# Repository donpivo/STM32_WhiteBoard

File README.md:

Description: https://retronics.no/tag/stm32whiteboard/

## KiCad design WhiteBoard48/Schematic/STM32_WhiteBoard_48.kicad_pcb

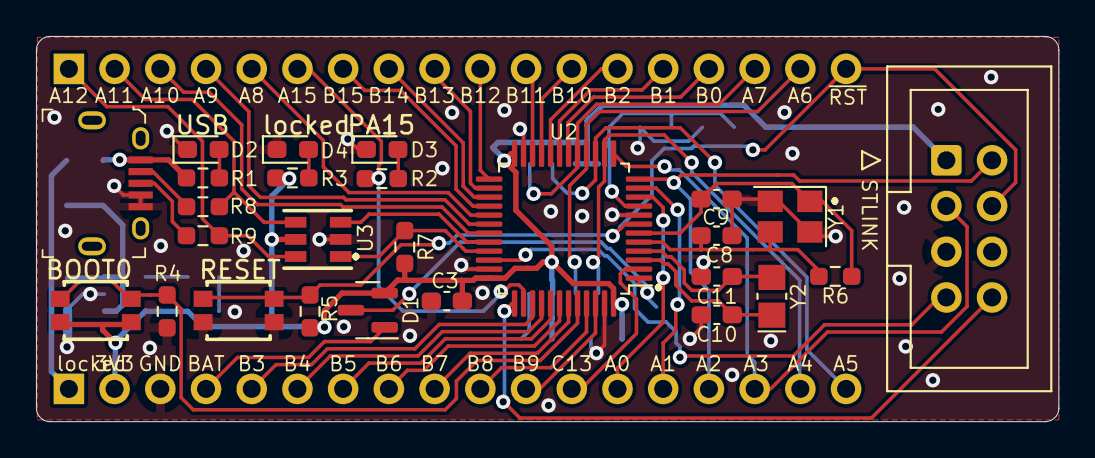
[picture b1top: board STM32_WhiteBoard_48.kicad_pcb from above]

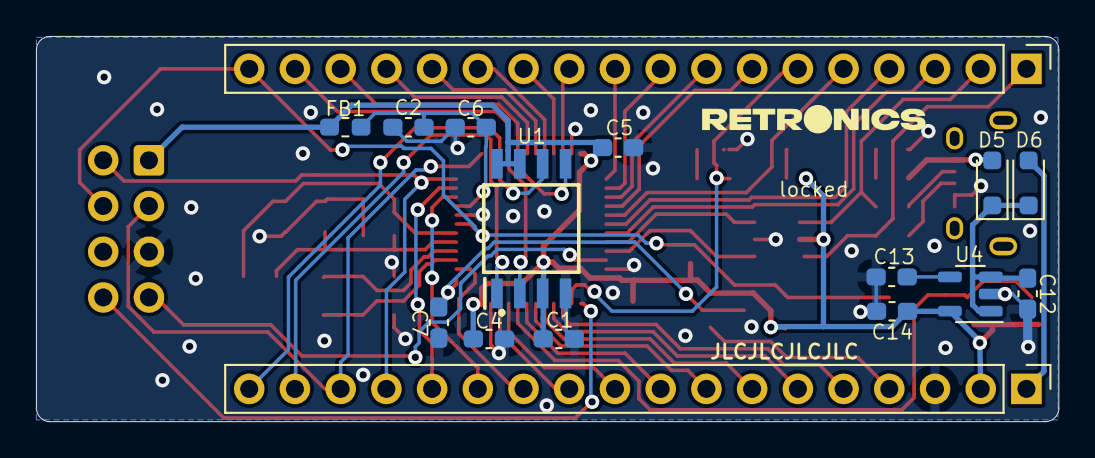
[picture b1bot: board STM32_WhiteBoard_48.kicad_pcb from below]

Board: 2 copper layers, 56.8 x 21.4 mm, 42 parts (16 on the bottom side), 55 nets.

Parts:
C1, C3, C4, C5, C6, C7: 100nF; C_0603_1608Metric_Pad1.08x0.95mm_HandSolder
C2, C12: 10µF; C_0603_1608Metric_Pad1.08x0.95mm_HandSolder
C8, C9, C10, C11: 20pF; C_0603_1608Metric_Pad1.08x0.95mm_HandSolder
C13: 10nF; C_0603_1608Metric_Pad1.08x0.95mm_HandSolder
C14: 1µF; C_0603_1608Metric_Pad1.08x0.95mm_HandSolder
D1: BAT54C; SOT-23
D2: "USB"; LED_0603_1608Metric_Pad1.05x0.95mm_HandSolder
D3: "PA15"; LED_0603_1608Metric_Pad1.05x0.95mm_HandSolder
D4: "3V3"; LED_0603_1608Metric_Pad1.05x0.95mm_HandSolder
D5, D6: B0520WS; D_SOD-323_HandSoldering
FB1: Ferrite_Bead_Small; L_0603_1608Metric_Pad1.05x0.95mm_HandSolder
J1: SWDIO+Serial; IDC-Header_2x04_P2.54mm_Vertical
J2: USB_B_Micro; USB_Micro_B_Female_10118194-0001LF
J3: Header2; PinHeader_1x18_P2.54mm_Vertical
J4: Header1; PinHeader_1x18_P2.54mm_Vertical
R1: 1kΩ; R_0603_1608Metric_Pad0.98x0.95mm_HandSolder
R2, R3: 330Ω; R_0603_1608Metric_Pad0.98x0.95mm_HandSolder
R4, R5: 10kΩ; R_0603_1608Metric_Pad0.98x0.95mm_HandSolder
R6: 1MΩ; R_0603_1608Metric_Pad0.98x0.95mm_HandSolder
R7: 1.5kΩ; R_0603_1608Metric_Pad0.98x0.95mm_HandSolder
R8, R9: 20Ω; R_0603_1608Metric_Pad0.98x0.95mm_HandSolder
SW1: BOOT0; SKTHACE010
SW2: RESET; SKTHACE010
U1: W25Q32JVSSIQ
U2: STM32F103CBTx; LQFP-48_7x7mm_P0.5mm
U3: USBLC6-2P6; USBLC6-2SC6
U4: LD3985M33R_SOT23; SOT-23-5
Y1: XC32M4-8.000; Crystal_SMD_3225-4Pin_3.2x2.5mm
Y2: CM8V-T1A-32.768KHZ-12.5PF; Crystal_SMD_MicroCrystal_CC8V-T1A-2Pin_2.0x1.2mm_HandSolder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

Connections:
+3.3V: C1.2, C3.1, C4.1, C5.1, C14.2, D1.2, FB1.2, J1.1, J4.2, R3.2, R5.2, R7.1, SW1.2, U1.3 (~WP), U1.7 (~RST), U1.8 (VCC), U2.24 (3V3), U2.36 (3V3), U2.48 (3V3), U3.5 (VBUS), U4.5 (VOUT)
+5V: D6.2 (A), J4.1
GND: C1.1, C2.1, C3.2, C4.2, C5.2, C6.1, C7.1, C8.1, C9.1, C10.2, C11.1, C12.1, C13.1, C14.1, D2.1 (K), D3.1 (K), D4.1 (K), J1.5, J2.4 (ID), J2.5 (GND), J4.3, R4.1, SW2.2, U1.4 (GND), U2.8 (GNDA), U2.23 (GND), U2.35 (GND), U2.47 (GND), U3.2 (GND), U4.2 (GND), Y1.2, Y1.4
unnamed: D2.2 (A), R1.1
unnamed: D3.2 (A), R2.1
unnamed: D4.2 (A), R3.1
unnamed: C12.2, D5.1 (K), D6.1 (K), U4.1 (VIN), U4.3 (INH)
unnamed: J2.3 (D+), R9.2
unnamed: J2.2 (D-), R8.2
unnamed: C2.2, C6.2, FB1.1, U2.9 (3V3A)
unnamed: R4.2, SW1.1, U2.44 (BOOT0)
unnamed: C10.1, U2.3 (OSC32K_A), Y2.1
unnamed: C11.2, U2.4 (OSC32K_B), Y2.2
unnamed: C8.2, R6.2, U2.5 (OSC_8M_A), Y1.3
unnamed: C9.2, R6.1, U2.6 (OSC_8M_B), Y1.1
unnamed: U2.32 (PA11_USB-), U3.3 (I/O2)
unnamed: R7.2, U2.33 (PA12_USB+), U3.1 (I/O1)
unnamed: C7.2, D1.3, U2.1 (VBAT)
unnamed: C13.2, U4.4 (BYP)
PA0: J4.13, U2.10 (PA0_ADC0_PWM)
PA1: J4.14, U2.11 (PA1_ADC1_PWM)
PA2_TX2: J1.2, J4.15, U2.12 (PA2_ADC2_TX2_PWM)
PA3_RX2: J1.3, J4.16, U2.13 (PA3_ADC3_RX2_PWM)
PA4_CS: J4.17, U1.1 (~CS), U2.14 (PA4_ADC4_SS1)
PA5_SCK1: J4.18, U1.6 (CLK), U2.15 (PA5_ADC5_SCK1)
PA6_MISO1: J3.17, U1.2 (DO), U2.16 (PA6_ADC6_MISO1_PWM)
PA7_MOSI1: J3.16, U1.5 (DI), U2.17 (PA7_ADC7_MOSI1_PWM)
PA8: J3.5, U2.29 (PA8_PWM)
PA9: J3.4, U2.30 (PA9_TX1_PWM)
PA10: J3.3, U2.31 (PA10_RX1_PWM)
PA11_USB-: J3.2, R8.1, U3.4 (I/O2)
PA12_USB+: J3.1, R9.1, U3.6 (I/O1)
PA13_SWDIO: J1.7, U2.34 (PA13_SWDIO)
PA14_SWCLK: J1.8, U2.37 (PA14_SWCLK)
PA15_LED: J3.6, R2.2, U2.38 (PA15)
PB0: J3.15, U2.18 (PB0_ADC8_PWM)
PB1: J3.14, U2.19 (PB1_ADC9_PWM)
PB2: J3.13, U2.20 (PB2)
PB3: J4.5, U2.39 (PB3_SCK1)
PB4: J4.6, U2.40 (PB4_MISO1)
PB5: J4.7, U2.41 (PB5_MOSI1)
PB6: J4.8, U2.42 (PB6_TX1_SCL1_PWM)
PB7: J4.9, U2.43 (PB7_RX1_SDA1_PWM)
PB8: J4.10, U2.45 (PB8_SCL1_PWM)
PB9: J4.11, U2.46 (PB9_SDA1_PWM)
PB10: J3.12, U2.21 (PB10_SCL2_TX3)
PB11: J3.11, U2.22 (PB11_SDA2_RX3)
PB12: J3.10, U2.25 (PB12_SS2)
PB13: J3.9, U2.26 (PB13_SCK2)
PB14: J3.8, U2.27 (PB14_MISO2)
PB15: J3.7, U2.28 (PB15_MOSI2)
PC13: J4.12, U2.2 (PC13)
RTC_BATT: D1.1, J4.4
VBUS: D5.2 (A), J2.1 (VBUS), R1.2
~RESET: J1.4, J3.18, R5.1, SW2.1, U2.7 (~RST)

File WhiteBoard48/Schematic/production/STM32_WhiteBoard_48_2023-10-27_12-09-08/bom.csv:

Designator,Footprint,Quantity,Value,LCSC Part #
"C1, C3, C4, C5, C6, C7",0603,6,100nF,
"C10, C11, C8, C9",0603,4,20pF,
"C12, C2",0603,2,10µF,
C13,0603,1,10nF,
C14,0603,1,1µF,
D1,SOT-23,1,BAT54C,
D2,0603,1,"""USB""",
D3,0603,1,"""PA15""",
D4,0603,1,"""3V3""",
"D5, D6",D_SOD-323_HandSoldering,2,B0520WS,
FB1,0603,1,Ferrite_Bead_Small,
J1,IDC-Header_2x04_P2.54mm_Vertical,1,SWDIO+Serial,
J2,USB_Micro_B_Female_10118194-0001LF,1,USB_B_Micro,
J3,PinHeader_1x18_P2.54mm_Vertical,1,Header2,
J4,PinHeader_1x18_P2.54mm_Vertical,1,Header1,
R1,0603,1,1kΩ,
"R2, R3",0603,2,330Ω,
"R4, R5",0603,2,10kΩ,
R6,0603,1,1MΩ,
R7,0603,1,1.5kΩ,
"R8, R9",0603,2,20Ω,
SW1,SKTHACE010,1,BOOT0,
SW2,SKTHACE010,1,RESET,
U1,W25Q32JVSSIQ,1,W25Q32JVSSIQ,
U2,LQFP-48_7x7mm_P0.5mm,1,STM32F103CBTx,
U3,USBLC6-2SC6,1,USBLC6-2P6,
U4,SOT-23-5,1,LD3985M33R_SOT23,
Y1,Crystal_SMD_3225-4Pin_3.2x2.5mm,1,XC32M4-8.000,
Y2,Crystal_SMD_MicroCrystal_CC8V-T1A-2Pin_2.0x1.2mm_HandSoldering,1,CM8V-T1A-32.768KHZ-12.5PF,

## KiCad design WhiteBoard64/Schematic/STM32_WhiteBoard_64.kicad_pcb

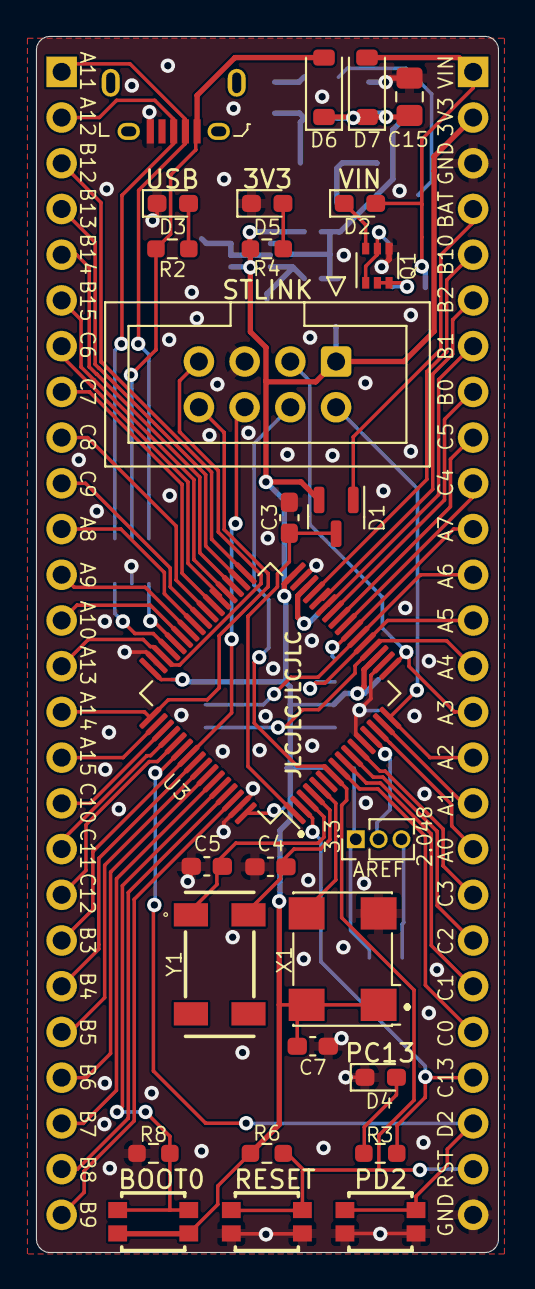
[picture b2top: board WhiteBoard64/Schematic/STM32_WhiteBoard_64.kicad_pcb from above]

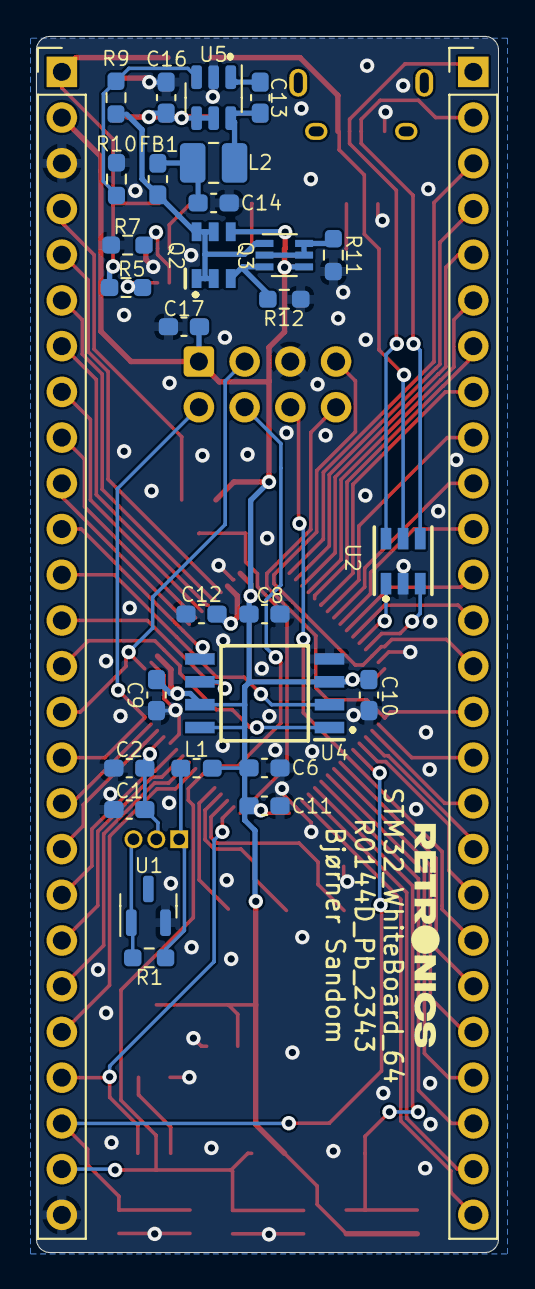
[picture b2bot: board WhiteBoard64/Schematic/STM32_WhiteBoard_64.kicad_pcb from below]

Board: 2 copper layers, 25.7 x 67.6 mm, 57 parts (30 on the bottom side), 77 nets.

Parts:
C1, C12: 4.7µF; C_0603_1608Metric_Pad1.08x0.95mm_HandSolder
C2, C3, C6, C7, C8, C9, C10, C11, C13, C16: 100nF; C_0603_1608Metric_Pad1.08x0.95mm_HandSolder
C4, C5: 4.7pF; C_0603_1608Metric_Pad1.08x0.95mm_HandSolder
C14, C17: 10µF 16V; C_0603_1608Metric_Pad1.08x0.95mm_HandSolder
C15: 10µF 50V; C_0805_2012Metric_Pad1.18x1.45mm_HandSolder
D1: BAT54C; SOT-23
D2: "VIN"; LED_0603_1608Metric_Pad1.05x0.95mm_HandSolder
D3: "USB"; LED_0603_1608Metric_Pad1.05x0.95mm_HandSolder
D4: "PC13"; LED_0603_1608Metric_Pad1.05x0.95mm_HandSolder
D5: "3V3"; LED_0603_1608Metric_Pad1.05x0.95mm_HandSolder
D6, D7: 1N5819W; D_SOD-123
FB1: 100Ω@100MHz; L_0603_1608Metric_Pad1.05x0.95mm_HandSolder
J1: SWDIO+Serial; IDC-Header_2x04_P2.54mm_Vertical
J2: USB_B_Micro; USB_Micro_B_Female_10118194-0001LF
J3: Header2; PinHeader_1x26_P2.54mm_Vertical
J4: Header1; PinHeader_1x26_P2.54mm_Vertical
JP1: Jumper_3_Bridged12; PinHeader_1x03_P1.27mm_Vertical
L1: 22µH 2.4Ω; L_0603_1608Metric_Pad1.05x0.95mm_HandSolder
L2: 6.8µH 1A; L_1008_2520Metric_Pad1.43x2.20mm_HandSolder
Q1: BC847BS; SOT-363_SC-70-6
Q2: Si3493DDV; SOT95P280X100-6N
Q3: BC857BS; SOT-363_SC-70-6-Handsoldering
R1: 220Ω; R_0603_1608Metric_Pad0.98x0.95mm_HandSolder
R2: 1kΩ; R_0603_1608Metric_Pad0.98x0.95mm_HandSolder
R3, R4: 330Ω; R_0603_1608Metric_Pad0.98x0.95mm_HandSolder
R5: 47kΩ; R_0603_1608Metric_Pad0.98x0.95mm_HandSolder
R6, R8, R11, R12: 10kΩ; R_0603_1608Metric_Pad0.98x0.95mm_HandSolder
R7: 270Ω; R_0603_1608Metric_Pad0.98x0.95mm_HandSolder
R9: 51kΩ; R_0603_1608Metric_Pad0.98x0.95mm_HandSolder
R10: 22.1kΩ; R_0603_1608Metric_Pad0.98x0.95mm_HandSolder
SW1: Boot0; SKTHACE010
SW2: Reset; SKTHACE010
SW3: User; SKTHACE010
U1: LM4040DIM3X-2.0; SOT-23
U2: USBLC6-2P6; USBLC6-2SC6
U3: STM32F411RET6; LQFP-64_10x10mm_P0.5mm
U4: W25Q32JVSSIQ
U5: TPS560430; SOT-23-6
X1: ASV-8MHz; Oscillator_SMD_Abracon_ASV-4Pin_7.0x5.1mm
Y1: ABS25-32.768KHZ-6-T; ABS25-Retronics22

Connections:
+3.3V: C6.2, C7.1, C8.2, C9.2, C10.2, C11.2, C17.2, D1.2, J1.1, J4.2, L1.1, Q2.4 (S), Q3.4 (E2), R4.2, R6.2, SW1.1, U3.19 (VDD), U3.32 (VDD), U3.48 (VDD), U3.64 (VDD), U4.3 (~WP), U4.7 (~RST), U4.8 (VCC), X1.1 (EN), X1.4 (Vdd)
/A11_USBD-: J2.2 (D-), J3.1, U2.6 (I/O1)
/A12_USBD+: J2.3 (D+), J3.2, U2.4 (I/O2)
/BOOT0: R8.2, SW1.2, U3.60 (BOOT0)
/PA0: J4.18, U3.14 (PA0-ADC-PWM)
/PA1: J4.17, U3.15 (PA1-ADC-PWM-SPI4:MOSI)
/PA2_UART2TX: J1.2, J4.16, U3.16 (PA2-ADC-UART2:TX)
/PA3_UART2RX: J1.3, J4.15, U3.17 (PA3-ADC-UART2:RX)
/PA4_CS: J4.14, U3.20 (PA4-ADC-SPI4:SSEL), U4.1 (~CS)
/PA5_SPI1CLK: J4.13, U3.21 (PA5-ADC-PWM-SPI1:SCLK), U4.6 (CLK)
/PA6_SPI1MISO: J4.12, U3.22 (PA6-ADC-PWM-SPI1:MISO), U4.2 (DO)
/PA7_SPI1MOSI: J4.11, U3.23 (PA7-ADC_PWM-SPI1:MOSI), U4.5 (DI)
/PA8: J3.11, U3.41 (PA8-PWM-USB:SOF-I2C3_SCL)
/PA9: J3.12, U3.42 (PA9-PWM-USB:VBUS-UART1:TX)
/PA10: J3.13, U3.43 (PA10-PWM-USB:ID-SPI5:MOSI-UART1:RX)
/PA13_SWDIO: J1.7, J3.14, U3.46 (PA13)
/PA14_SWCLK: J1.8, J3.15, U3.49 (PA14)
/PA15: J3.16, U3.50 (PA15-PWM-UART1:TX-SPI1:SSEL)
/PB0: J4.8, U3.26 (PB0-ADC-PWM-SPI5:SCLK)
/PB1: J4.7, U3.27 (PB1-PWM-ADC-SPI5:SSEL)
/PB2: J4.6, U3.28 (PB2)
/PB3_SWO: J1.6, J3.20, U3.55 (PB3-PWM-UART1:RX-SPI3:SCLK-I2C2:SDA)
/PB4: J3.21, U3.56 (PB4-PWM-SPI3:MISO-I2C3:SDA)
/PB5: J3.22, U3.57 (PB5-PWM-SPI3:MOSI)
/PB6: J3.23, U3.58 (PB6-PWM-UART1:TX-I2C1:SCL)
/PB7: J3.24, U3.59 (PB7-PWM-UART1:RX-I2C1:SDA)
/PB8: J3.25, U3.61 (PB8-PWM-SPI5:MOSI-I2C1:SCL)
/PB9: J3.26, U3.62 (PB9-PWM-SPI2:SSEL-I2C1:SDA)
/PB10: J4.5, U3.29 (PB10-PWM-SPI2:SCLK-I2C2:SCL)
/PB12: J3.3, U3.33 (PB12-SPI2_SSEL)
/PB13: J3.4, U3.34 (PB13-PWM-SPI2:SCLK)
/PB14: J3.5, U3.35 (PB14-PWM-SPI2:MISO)
/PB15: J3.6, U3.36 (PB15-PWM-SPI2:MOSI)
/PC0: J4.22, U3.8 (PC0-ADC)
/PC1: J4.21, U3.9 (PC1-ADC)
/PC2: J4.20, U3.10 (PC2-ADC-SPI2:MISO)
/PC3: J4.19, U3.11 (PC3-ADC-SPI2:MOSI)
/PC4: J4.10, U3.24 (PC4-ADC)
/PC5: J4.9, U3.25 (PC5-ADC)
/PC6: J3.7, U3.37 (PC6-PWM-UART6:TX)
/PC7: J3.8, U3.38 (PC7-PWM-SPI2:SCLK-UART6:RX)
/PC8: J3.9, U3.39 (PC8-PWM)
/PC9: J3.10, U3.40 (PC9)
/PC10: J3.17, U3.51 (PC10-SPI3:SCLK)
/PC11: J3.18, U3.52 (PC11-SPI3:MISO)
/PC12: J3.19, U3.53 (PC12-SPI3:MOSI)
/PC13_LED: J4.23, R3.2, U3.2 (PC13)
/PD2_USERBTN: J4.24, SW3.2, U3.54 (PD2)
/RTC_BATT: D1.1, J4.4
/VBAT: C3.1, D1.3, U3.1 (VBAT)
/~RESET: J1.4, J4.25, R6.1, SW2.2, U3.7 (~RESET)
GND: C1.1, C2.1, C3.2, C4.2, C5.2, C6.1, C7.2, C8.1, C9.1, C10.1, C11.1, C12.1, C14.1, C15.1, C16.1, C17.1, D3.1 (K), D4.1 (K), D5.1 (K), J1.5, J2.5 (GND), J4.3, J4.26, Q1.4 (E2), R7.1, R8.1, R10.2, R11.1, R12.1, SW2.1, SW3.1, U1.2 (A), U2.2 (GND), U3.12 (VSSA), U3.18 (VSS), U3.31 (VSS), U3.47 (VSS), U3.63 (VSS), U4.4 (GND), U5.2 (GND), X1.2 (GND)
unnamed: C14.2, FB1.2, L2.2
unnamed: D2.1 (K), Q1.6 (C1)
unnamed: D3.2 (A), R2.1
unnamed: D4.2 (A), R3.1
unnamed: D5.2 (A), R4.1
unnamed: C15.2, C16.2, D6.1 (K), D7.1 (K), U5.4 (EN), U5.5 (VIN)
unnamed: JP1.1 (A), L1.2, R1.1
unnamed: JP1.3 (B), R1.2, U1.1 (K)
unnamed: C1.2, C2.2, JP1.2 (C), U3.13 (VDDA)
unnamed: Q1.2 (B1), Q1.3 (C2), R5.1
unnamed: Q1.1 (E1), Q1.5 (B2), R7.2
unnamed: Q2.3 (G), Q3.3 (C2), R12.2
unnamed: Q3.2 (B1), Q3.5 (B2), Q3.6 (C1), R11.2
unnamed: FB1.1, Q2.1 (D), Q2.2 (D), Q2.5 (D), Q2.6 (D), Q3.1 (E1), R9.1
unnamed: U3.5 (OSC8M_IN_(PD0)), X1.3 (OUT)
unnamed: C5.1, U3.3 (OSC32_IN_(PC14)), Y1.1
unnamed: C4.1, U3.4 (OSC32_OUT_(PC15)), Y1.4
unnamed: U2.1 (I/O1), U3.44 (PA11-PWM-UART6:TX-SPI4:MISO-USB:DM)
unnamed: U2.3 (I/O2), U3.45 (PA12-UART6:RX-UART1:RTS-SPI5:MISO-USB:DP)
unnamed: C12.2, U3.30 (VCAP1)
unnamed: C13.2, U5.1 (CB)
unnamed: R9.2, R10.1, U5.3 (FB)
unnamed: C13.1, L2.1, U5.6 (SW)
VBUS: D6.2 (A), J2.1 (VBUS), R2.2, U2.5 (VBUS)
VCC: D2.2 (A), D7.2 (A), J4.1, R5.2

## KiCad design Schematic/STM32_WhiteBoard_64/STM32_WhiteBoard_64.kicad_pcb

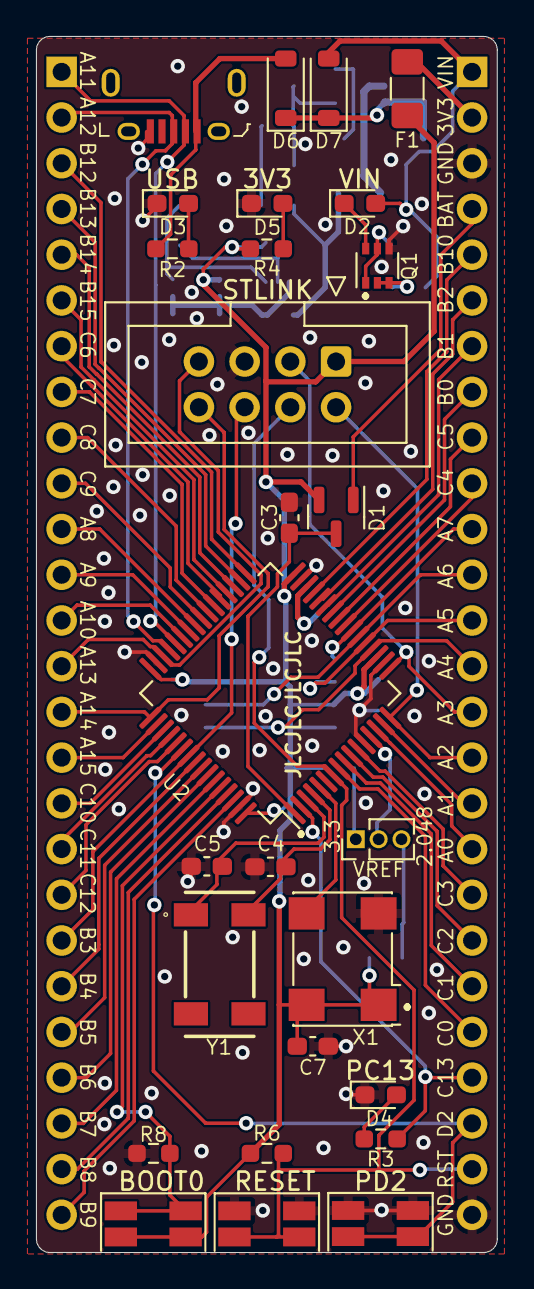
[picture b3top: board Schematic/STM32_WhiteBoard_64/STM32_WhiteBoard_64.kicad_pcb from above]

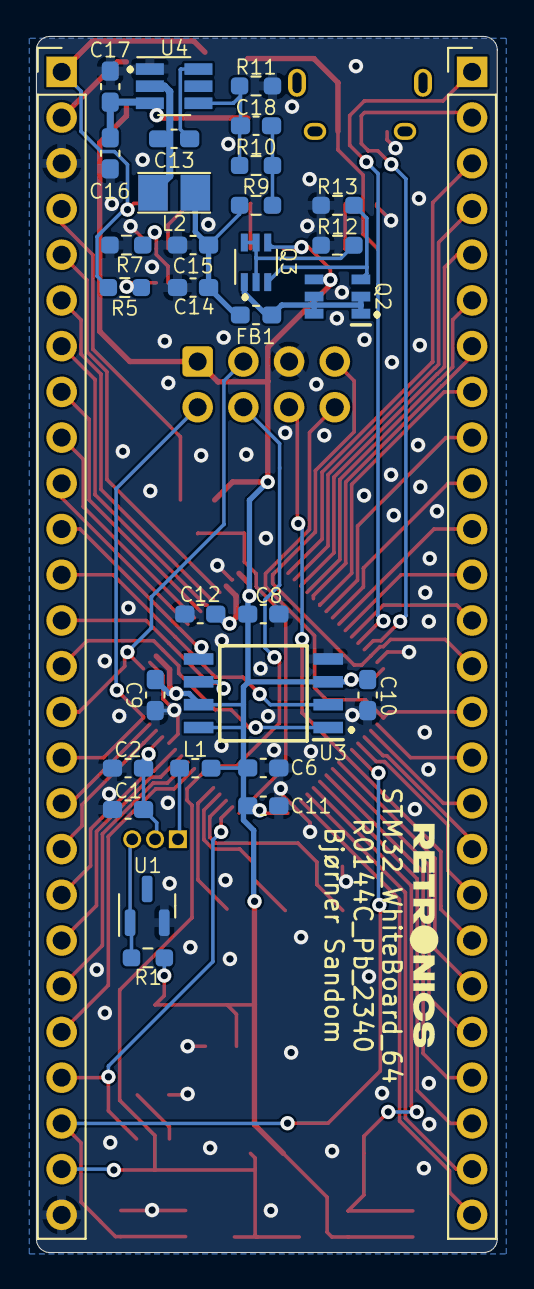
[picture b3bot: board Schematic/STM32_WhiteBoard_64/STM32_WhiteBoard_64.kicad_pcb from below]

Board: 2 copper layers, 25.6 x 67.6 mm, 59 parts (32 on the bottom side), 77 nets.

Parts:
C1: 10µF; C_0603_1608Metric_Pad1.08x0.95mm_HandSolder
C2, C3, C6, C7, C8, C9, C10, C11, C13, C17: 100nF; C_0603_1608Metric_Pad1.08x0.95mm_HandSolder
C4, C5: 4.7pF; C_0603_1608Metric_Pad1.08x0.95mm_HandSolder
C12: 4.7µF; C_0603_1608Metric_Pad1.08x0.95mm_HandSolder
C14, C15: 22µF 10V; C_0603_1608Metric_Pad1.08x0.95mm_HandSolder
C16: 10µF 35V; C_0603_1608Metric_Pad1.08x0.95mm_HandSolder
C18: 75pF; C_0603_1608Metric_Pad1.08x0.95mm_HandSolder
D1: BAT54C; SOT-23
D2: "VIN"; LED_0603_1608Metric_Pad1.05x0.95mm_HandSolder
D3: "USB"; LED_0603_1608Metric_Pad1.05x0.95mm_HandSolder
D4: "PC13"; LED_0603_1608Metric_Pad1.05x0.95mm_HandSolder
D5: "3V3"; LED_0603_1608Metric_Pad1.05x0.95mm_HandSolder
D6, D7: 1N5819W; D_SOD-123
F1: 1A; Fuse_1206_3216Metric_Pad1.42x1.75mm_HandSolder
FB1: 100Ω@100MHz 30mΩ@DC; L_0603_1608Metric_Pad1.05x0.95mm_HandSolder
J1: SWDIO+Serial; IDC-Header_2x04_P2.54mm_Vertical
J2: USB_B_Micro; USB_Micro_B_Female_10118194-0001LF
J3: Header2; PinHeader_1x26_P2.54mm_Vertical
J4: Header1; PinHeader_1x26_P2.54mm_Vertical
JP1: Jumper_3_Bridged12; PinHeader_1x03_P1.27mm_Vertical
L1: 22µH 2.4Ω; L_0603_1608Metric_Pad1.05x0.95mm_HandSolder
L2: 10µH 1A; L_Taiyo-Yuden_NR-20xx_HandSoldering
Q1: BC847BS; SOT-363_SC-70-6
Q2: Si3493DDV; SOT95P280X100-6N
Q3: BC857BS; SOT-363_SC-70-6-Handsoldering
R1: 220Ω; R_0603_1608Metric_Pad0.98x0.95mm_HandSolder
R2: 1kΩ; R_0603_1608Metric_Pad0.98x0.95mm_HandSolder
R3, R4: 330Ω; R_0603_1608Metric_Pad0.98x0.95mm_HandSolder
R5: 47kΩ; R_0603_1608Metric_Pad0.98x0.95mm_HandSolder
R6, R8, R12, R13: 10kΩ; R_0603_1608Metric_Pad0.98x0.95mm_HandSolder
R7: 270Ω; R_0603_1608Metric_Pad0.98x0.95mm_HandSolder
R9: 49.9Ω; R_0603_1608Metric_Pad0.98x0.95mm_HandSolder
R10: 100kΩ; R_0603_1608Metric_Pad0.98x0.95mm_HandSolder
R11: 22kΩ; R_0603_1608Metric_Pad0.98x0.95mm_HandSolder
SW1: Boot0; PTS840ESDGMSMTRLFS
SW2: Reset; PTS840ESDGMSMTRLFS
SW3: User; PTS840ESDGMSMTRLFS
U1: LM4040DIM3X-2.0; SOT-23
U2: STM32F411RET6; LQFP-64_10x10mm_P0.5mm
U3: W25Q32JVSSIQ
U4: TPS54302; SOT-23-6_Handsoldering
X1: ASV-8MHz; Oscillator_SMD_Abracon_ASV-4Pin_7.0x5.1mm
Y1: ABS25-32.768KHZ-6-T; ABS25-Retronics22

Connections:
+3.3V: C6.2, C7.1, C8.2, C9.2, C10.2, C11.2, D1.2, F1.1, J1.1, L1.1, Q2.4 (S), Q3.4 (E2), R1.1, R4.2, R6.2, SW1.2, U2.19 (VDD), U2.32 (VDD), U2.48 (VDD), U2.64 (VDD), U3.3 (~WP), U3.7 (~RST), U3.8 (VCC), X1.1 (EN), X1.4 (Vdd)
/A11: J2.2 (D-), J3.1, U2.44 (PA11-PWM-UART6:TX-SPI4:MISO-USB:DM)
/A12: J2.3 (D+), J3.2, U2.45 (PA12-UART6:RX-UART1:RTS-SPI5:MISO-USB:DP)
/BOOT0: R8.2, SW1.1, U2.60 (BOOT0)
/PA0: J4.18, U2.14 (PA0-ADC-PWM)
/PA1: J4.17, U2.15 (PA1-ADC-PWM-SPI4:MOSI)
/PA2: J1.2, J4.16, U2.16 (PA2-ADC-UART2:TX)
/PA3: J1.3, J4.15, U2.17 (PA3-ADC-UART2:RX)
/PA4: J4.14, U2.20 (PA4-ADC-SPI4:SSEL), U3.1 (~CS)
/PA5: J4.13, U2.21 (PA5-ADC-PWM-SPI1:SCLK), U3.6 (CLK)
/PA6: J4.12, U2.22 (PA6-ADC-PWM-SPI1:MISO), U3.2 (DO)
/PA7: J4.11, U2.23 (PA7-ADC_PWM-SPI1:MOSI), U3.5 (DI)
/PA8: J3.11, U2.41 (PA8-PWM-USB:SOF-I2C3_SCL)
/PA9: J3.12, U2.42 (PA9-PWM-USB:VBUS-UART1:TX)
/PA10: J3.13, U2.43 (PA10-PWM-USB:ID-SPI5:MOSI-UART1:RX)
/PA13: J1.7, J3.14, U2.46 (PA13)
/PA14: J1.8, J3.15, U2.49 (PA14)
/PA15: J3.16, U2.50 (PA15-PWM-UART1:TX-SPI1:SSEL)
/PB0: J4.8, U2.26 (PB0-ADC-PWM-SPI5:SCLK)
/PB1: J4.7, U2.27 (PB1-PWM-ADC-SPI5:SSEL)
/PB2: J4.6, U2.28 (PB2)
/PB3: J1.6, J3.20, U2.55 (PB3-PWM-UART1:RX-SPI3:SCLK-I2C2:SDA)
/PB4: J3.21, U2.56 (PB4-PWM-SPI3:MISO-I2C3:SDA)
/PB5: J3.22, U2.57 (PB5-PWM-SPI3:MOSI)
/PB6: J3.23, U2.58 (PB6-PWM-UART1:TX-I2C1:SCL)
/PB7: J3.24, U2.59 (PB7-PWM-UART1:RX-I2C1:SDA)
/PB8: J3.25, U2.61 (PB8-PWM-SPI5:MOSI-I2C1:SCL)
/PB9: J3.26, U2.62 (PB9-PWM-SPI2:SSEL-I2C1:SDA)
/PB10: J4.5, U2.29 (PB10-PWM-SPI2:SCLK-I2C2:SCL)
/PB12: J3.3, U2.33 (PB12-SPI2_SSEL)
/PB13: J3.4, U2.34 (PB13-PWM-SPI2:SCLK)
/PB14: J3.5, U2.35 (PB14-PWM-SPI2:MISO)
/PB15: J3.6, U2.36 (PB15-PWM-SPI2:MOSI)
/PC0: J4.22, U2.8 (PC0-ADC)
/PC1: J4.21, U2.9 (PC1-ADC)
/PC2: J4.20, U2.10 (PC2-ADC-SPI2:MISO)
/PC3: J4.19, U2.11 (PC3-ADC-SPI2:MOSI)
/PC4: J4.10, U2.24 (PC4-ADC)
/PC5: J4.9, U2.25 (PC5-ADC)
/PC6: J3.7, U2.37 (PC6-PWM-UART6:TX)
/PC7: J3.8, U2.38 (PC7-PWM-SPI2:SCLK-UART6:RX)
/PC8: J3.9, U2.39 (PC8-PWM)
/PC9: J3.10, U2.40 (PC9)
/PC10: J3.17, U2.51 (PC10-SPI3:SCLK)
/PC11: J3.18, U2.52 (PC11-SPI3:MISO)
/PC12: J3.19, U2.53 (PC12-SPI3:MOSI)
/PC13: J4.23, R3.2, U2.2 (PC13)
/PD2: J4.24, SW3.2, U2.54 (PD2)
/RTC_BATT: D1.1, J4.4
/VBAT: C3.1, D1.3, U2.1 (VBAT)
/~RESET: J1.4, J4.25, R6.1, SW2.2, U2.7 (~RESET)
GND: C1.1, C2.1, C3.2, C4.2, C5.2, C6.1, C7.2, C8.1, C9.1, C10.1, C11.1, C12.1, C14.1, C15.1, C16.1, C17.1, D3.1 (K), D4.1 (K), D5.1 (K), J1.5, J2.5 (GND), J4.3, J4.26, Q1.4 (E2), R7.1, R8.1, R11.2, R12.1, R13.1, SW2.1, SW3.1, U1.2 (A), U2.12 (VSSA), U2.18 (VSS), U2.31 (VSS), U2.47 (VSS), U2.63 (VSS), U3.4 (GND), U4.1 (GND), X1.2 (GND)
unnamed: C14.2, C15.2, FB1.1, L2.2, R9.1
unnamed: C18.2, R9.2, R10.1
unnamed: D2.1 (K), Q1.6 (C1)
unnamed: D3.2 (A), R2.1
unnamed: D4.2 (A), R3.1
unnamed: D5.2 (A), R4.1
unnamed: C16.2, C17.2, D6.1 (K), D7.1 (K), U4.3 (VIN)
unnamed: F1.2, J4.2
unnamed: JP1.1 (A), L1.2
unnamed: JP1.3 (B), R1.2, U1.1 (K)
unnamed: C1.2, C2.2, JP1.2 (C), U2.13 (VDDA)
unnamed: Q1.2 (B1), Q1.3 (C2), R5.1
unnamed: Q1.1 (E1), Q1.5 (B2), R7.2
unnamed: Q2.3 (G), Q3.3 (C2), R13.2
unnamed: Q3.2 (B1), Q3.5 (B2), Q3.6 (C1), R12.2
unnamed: FB1.2, Q2.1 (D), Q2.2 (D), Q2.5 (D), Q2.6 (D), Q3.1 (E1)
unnamed: U2.5 (OSC8M_IN_(PD0)), X1.3 (OUT)
unnamed: C5.1, U2.3 (OSC32_IN_(PC14)), Y1.1
unnamed: C4.1, U2.4 (OSC32_OUT_(PC15)), Y1.4
unnamed: C12.2, U2.30 (VCAP1)
unnamed: C13.2, U4.6 (BOOT)
unnamed: C18.1, R10.2, R11.1, U4.4 (FB)
unnamed: C13.1, L2.1, U4.2 (SW)
VBUS: D6.2 (A), J2.1 (VBUS), R2.2
VCC: D2.2 (A), D7.2 (A), J4.1, R5.2

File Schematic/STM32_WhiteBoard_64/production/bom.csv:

Designator,Footprint,Quantity,Value,LCSC Part #
C1,0603,1,10µF,
"C10, C11, C13, C17, C2, C3, C6, C7, C8, C9",0603,10,100nF,
C12,0603,1,4.7µF,
"C14, C15",0603,2,22µF 10V,
C16,0603,1,10µF 35V,
C18,0603,1,75pF,
"C4, C5",0603,2,4.7pF,
D1,SOT-23,1,BAT54C,
D2,0603,1,"""VIN""",
D3,0603,1,"""USB""",
D4,0603,1,"""PC13""",
D5,0603,1,"""3V3""",
"D6, D7",D_SOD-123,2,1N5819W,
F1,1206,1,1A,
FB1,0603,1,100Ω@100MHz 30mΩ@DC,
J1,IDC-Header_2x04_P2.54mm_Vertical,1,SWDIO+Serial,
J2,USB_Micro_B_Female_10118194-0001LF,1,USB_B_Micro,
J3,PinHeader_1x26_P2.54mm_Vertical,1,Header2,
J4,PinHeader_1x26_P2.54mm_Vertical,1,Header1,
JP1,PinHeader_1x03_P1.27mm_Vertical,1,Jumper_3_Bridged12,
L1,0603,1,22µH 2.4Ω,
L2,L_Taiyo-Yuden_NR-20xx_HandSoldering,1,10µH 1A,
Q1,SOT-363_SC-70-6,1,BC847BS,
Q2,SOT95P280X100-6N,1,Si3493DDV,
Q3,SOT-363_SC-70-6-Handsoldering,1,BC857BS,
R1,0603,1,220Ω,
R10,0603,1,100kΩ,
R11,0603,1,22kΩ,
"R12, R13, R6, R8",0603,4,10kΩ,
R2,0603,1,1kΩ,
"R3, R4",0603,2,330Ω,
R5,0603,1,47kΩ,
R7,0603,1,270Ω,
R9,0603,1,49.9Ω,
SW1,PTS840ESDGMSMTRLFS,1,Boot0,
SW2,PTS840ESDGMSMTRLFS,1,Reset,
SW3,PTS840ESDGMSMTRLFS,1,User,
U1,SOT-23,1,LM4040DIM3X-2.0,
U2,LQFP-64_10x10mm_P0.5mm,1,STM32F411RET6,
U3,W25Q32JVSSIQ,1,W25Q32JVSSIQ,
U4,SOT-23-6_Handsoldering,1,TPS54302,
X1,Oscillator_SMD_Abracon_ASV-4Pin_7.0x5.1mm,1,ASV-8MHz,
Y1,ABS25-Retronics22,1,ABS25-32.768KHZ-6-T,

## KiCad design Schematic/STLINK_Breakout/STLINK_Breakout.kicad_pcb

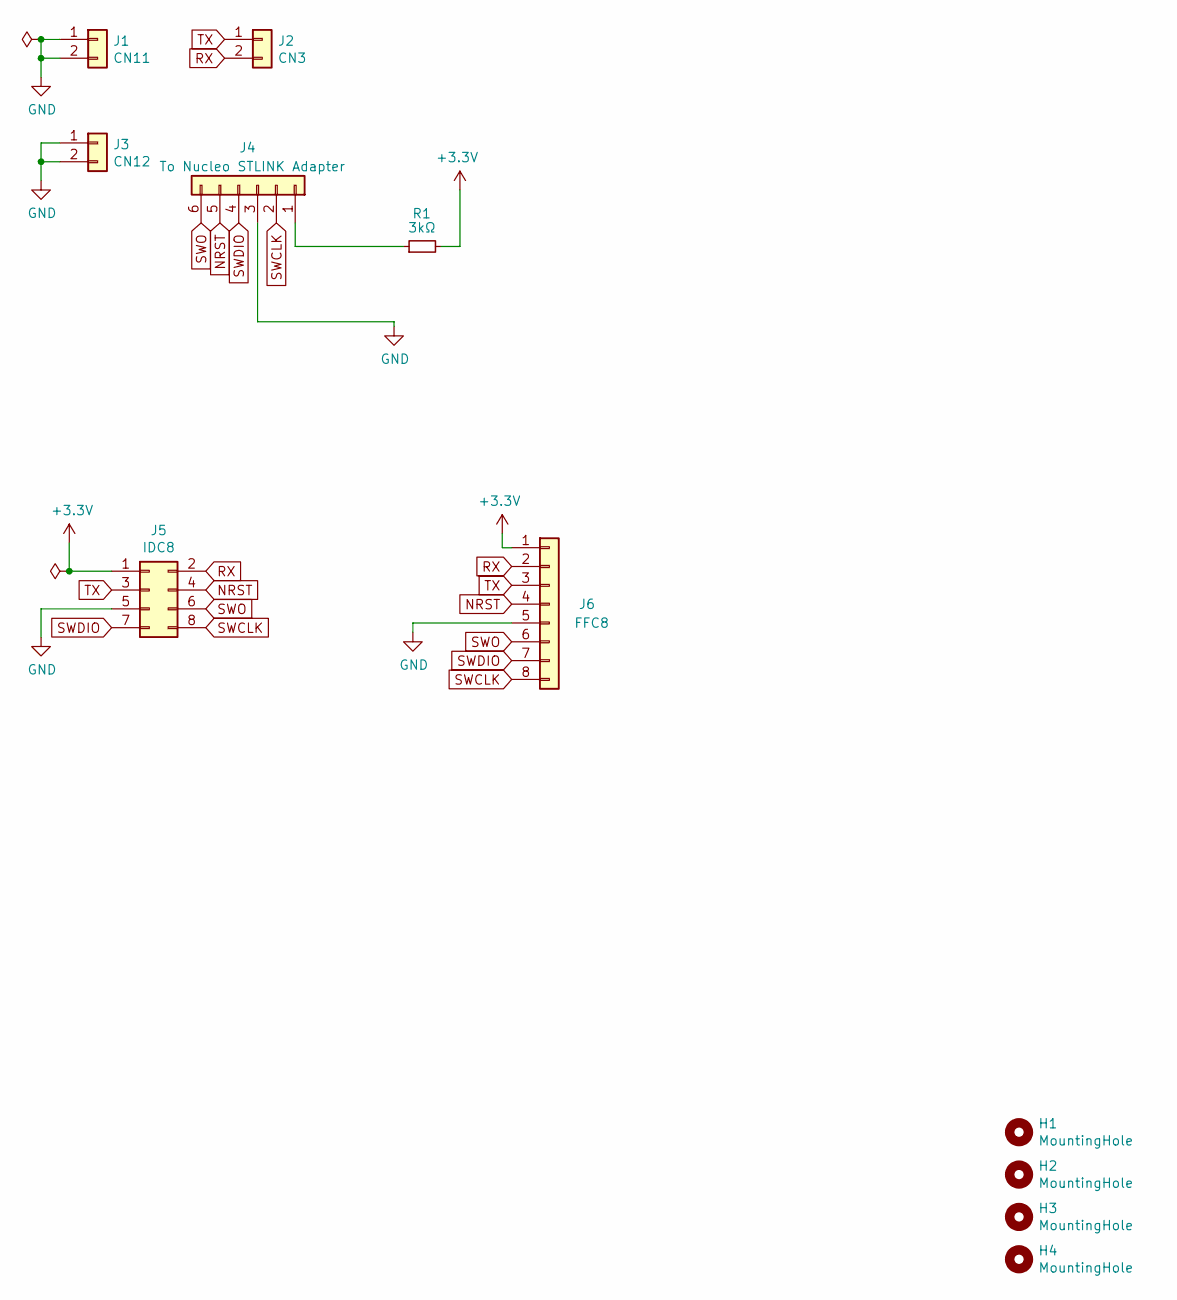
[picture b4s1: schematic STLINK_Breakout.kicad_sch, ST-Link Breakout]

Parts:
H1, H2, H3, H4: MountingHole; MountingHole_3.2mm_M3
J1: CN11; PinSocket_1x02_P2.54mm_Vertical
J2: CN3; PinSocket_1x02_P2.54mm_Vertical
J3: CN12; PinSocket_1x02_P2.54mm_Vertical
J4: To Nucleo STLINK Adapter; PinSocket_1x06_P2.54mm_Vertical
J5: IDC8; IDC-Header_2x04_P2.54mm_Vertical
J6: FFC8; 0527450897
R1: 3kΩ; R_0603_1608Metric_Pad0.98x0.95mm_HandSolder

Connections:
+3.3V: J5.1, J6.1, R1.2
GND: J1.1, J1.2, J3.1, J3.2, J4.3, J5.5, J6.5
NRST: J4.5, J5.4, J6.4
unnamed: J4.1, R1.1
RX: J2.2, J5.2, J6.2
SWCLK: J4.2, J5.8, J6.8
SWDIO: J4.4, J5.7, J6.7
SWO: J4.6, J5.6, J6.6
TX: J2.1, J5.3, J6.3

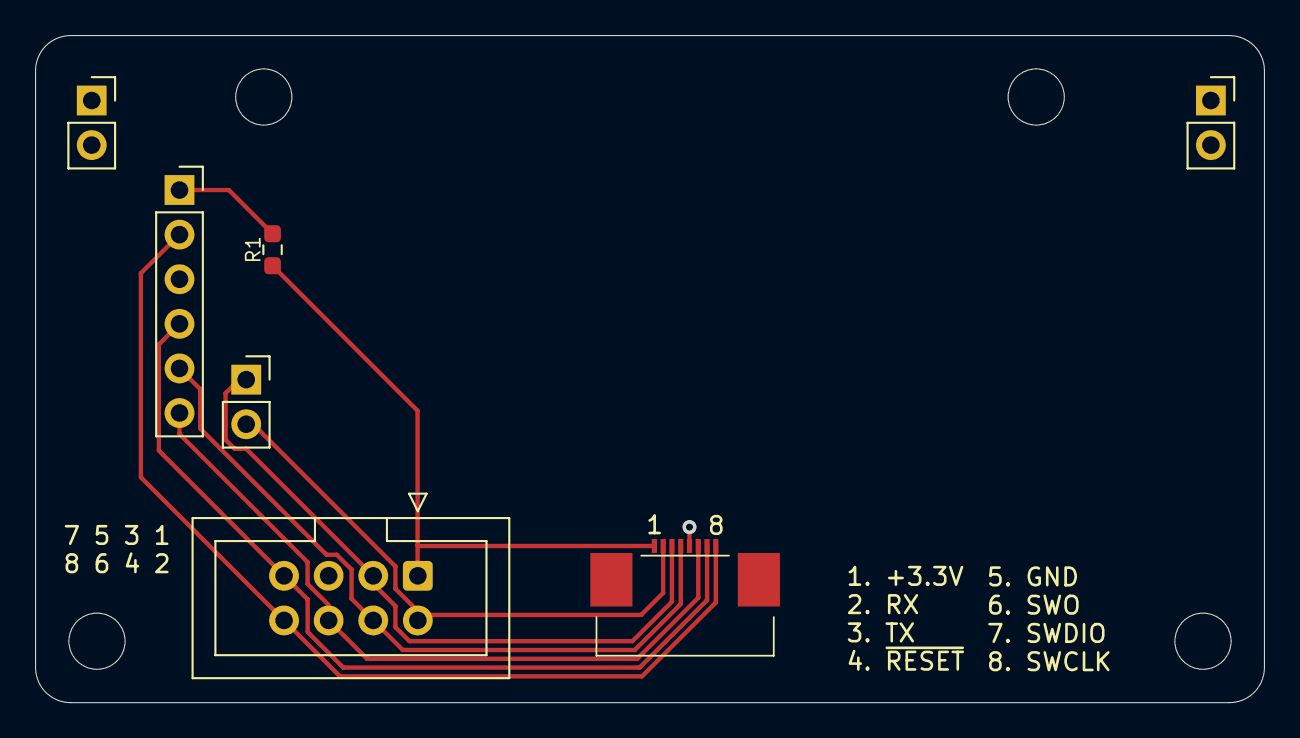
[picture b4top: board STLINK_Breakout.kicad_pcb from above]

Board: 2 copper layers, 70.0 x 38.0 mm, 11 parts (0 on the bottom side), 9 nets.

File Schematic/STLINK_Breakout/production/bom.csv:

Designator,Footprint,Quantity,Value,LCSC Part #
C1,0603,1,100nF,
"H1, H2, H3, H4",MountingHole_3.2mm_M3,4,MountingHole,
J1,PinSocket_1x02_P2.54mm_Vertical,1,CN11,
J2,PinSocket_1x02_P2.54mm_Vertical,1,CN3,
J3,PinSocket_1x02_P2.54mm_Vertical,1,CN12,
J4,PinSocket_1x06_P2.54mm_Vertical,1,To Nucleo STLINK Adapter,
J5,IDC-Header_2x04_P2.54mm_Vertical,1,IDC8,
J6,0527450897,1,FFC8,
R1,0603,1,4.7kΩ,

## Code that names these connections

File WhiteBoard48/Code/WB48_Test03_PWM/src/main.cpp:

#include <Arduino.h>
#define PIN_PWM0A PB0
#define PIN_PWM1A PB1
#define PIN_PWM2A PB6
#define PIN_PWM3A PB7
#define PIN_PWM4A PB8
#define PIN_PWM5A PB9
#define PIN_PWM6A PA0 
#define PIN_PWM6B PA1
uint8_t pwmValue;
HardwareSerial uart2(PA3, PA2);

void setup() 
{
  uart2.begin(115200);
  uart2.println("PWM Test");
  pinMode(PIN_PWM0A, OUTPUT);
  pinMode(PIN_PWM1A, OUTPUT);
  pinMode(PIN_PWM2A, OUTPUT);
  pinMode(PIN_PWM3A, OUTPUT);
  pinMode(PIN_PWM4A, OUTPUT);
  pinMode(PIN_PWM5A, OUTPUT);
  pinMode(PIN_PWM6A, OUTPUT);
  pinMode(PIN_PWM6B, OUTPUT);
  analogWriteFrequency(20000);

}

void loop() 
{
  pwmValue++;
  if(pwmValue>=255) pwmValue=0;
  analogWrite(PIN_PWM0A,pwmValue);
  analogWrite(PIN_PWM1A,pwmValue);
  analogWrite(PIN_PWM2A,pwmValue);
  analogWrite(PIN_PWM3A,pwmValue);
  analogWrite(PIN_PWM4A,pwmValue);
  analogWrite(PIN_PWM5A,pwmValue);
  analogWrite(PIN_PWM6A,pwmValue);
  analogWrite(PIN_PWM6B,pwmValue);
  delay(10);
}

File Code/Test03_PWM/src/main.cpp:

#include <Arduino.h>
#define PIN_PWM0A PB7
#define PIN_PWM1A PB6
#define PIN_PWM2A PB5
#define PIN_PWM3A PB4
#define PIN_PWM4A PA15
#define PIN_PWM5A PA11
#define PIN_PWM6A PA10 
#define PIN_PWM6B PC8
#define PIN_PWM7A PB10 
#define PIN_PWM7B PB14

uint8_t pwmValue;

void setup() 
{
  Serial.begin(115200);
  Serial.println("PWM Test");
  pinMode(PIN_PWM0A, OUTPUT);
  pinMode(PIN_PWM1A, OUTPUT);
  pinMode(PIN_PWM2A, OUTPUT);
  pinMode(PIN_PWM3A, OUTPUT);
  pinMode(PIN_PWM4A, OUTPUT);
  pinMode(PIN_PWM5A, OUTPUT);
  pinMode(PIN_PWM6A, OUTPUT);
  pinMode(PIN_PWM6B, OUTPUT);
  pinMode(PIN_PWM7A, OUTPUT);
  pinMode(PIN_PWM7B, OUTPUT);
  analogWriteFrequency(20000);

}

void loop() 
{
  pwmValue++;
  if(pwmValue>=255) pwmValue=0;
  analogWrite(PIN_PWM0A,pwmValue);
  analogWrite(PIN_PWM1A,pwmValue);
  analogWrite(PIN_PWM2A,pwmValue);
  analogWrite(PIN_PWM3A,pwmValue);
  analogWrite(PIN_PWM4A,pwmValue);
  analogWrite(PIN_PWM5A,pwmValue);
  analogWrite(PIN_PWM6A,pwmValue);
  analogWrite(PIN_PWM6B,pwmValue);
  analogWrite(PIN_PWM7A,pwmValue);
  analogWrite(PIN_PWM7B,pwmValue);
  delay(10);
}

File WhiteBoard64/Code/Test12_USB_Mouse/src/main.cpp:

#include <Arduino.h>

#include "Mouse.h"

// set pin numbers for the five buttons:
const int upButton = PC0;
const int downButton = PC1;
const int leftButton = PC2;
const int rightButton = PC3;
const int mouseButton = PD2;

int range = 5;           // output range of X or Y movement; affects movement speed
int responseDelay = 10;  // response delay of the mouse, in ms


void setup() {
  // initialize the buttons' inputs:
  pinMode(upButton, INPUT_PULLUP);
  pinMode(downButton, INPUT_PULLUP);
  pinMode(leftButton, INPUT_PULLUP);
  pinMode(rightButton, INPUT_PULLUP);
  pinMode(mouseButton, INPUT_PULLUP);
  // initialize mouse control:
  Mouse.begin();
}

void loop() {
  // read the buttons:
  int upState = !digitalRead(upButton);
  int downState = !digitalRead(downButton);
  int rightState = !digitalRead(rightButton);
  int leftState = !digitalRead(leftButton);
  int clickState = !digitalRead(mouseButton);

  // calculate the movement distance based on the button states:
  int xDistance = (leftState - rightState) * range;
  int yDistance = (upState - downState) * range;

  // if X or Y is non-zero, move:
  if ((xDistance != 0) || (yDistance != 0)) {
    Mouse.move(xDistance, yDistance, 0);
  }

  // if the mouse button is pressed:
  if (clickState == HIGH) {
    // if the mouse is not pressed, press it:
    if (!Mouse.isPressed(MOUSE_LEFT)) {
      Mouse.press(MOUSE_LEFT);
    }
  }
  // else the mouse button is not pressed:
  else {
    // if the mouse is pressed, release it:
    if (Mouse.isPressed(MOUSE_LEFT)) {
      Mouse.release(MOUSE_LEFT);
    }
  }

  // a delay so the mouse doesn't move too fast:
  delay(responseDelay);
}

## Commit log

2023-08-25 Added flash memory
2023-09-06 Changed footprints for D6, D7
2023-09-06 Updated production files
2023-09-06 Added datasheets
2023-09-06 Updated symbols
2023-09-06 Changed component value
2023-09-11 Added pull-up resistor for Reset
2023-09-28 Basic IO tests
2023-09-28 Changed resistor value
2023-09-30 Added voltage reference
2023-09-30 Minor layout changes
2023-10-02 Added btn PD2, added fuse, removed hardware watchdog
2023-10-02 File cleanup
2023-10-15 Added basic code examples
2023-10-15 Minor silkscreen updates
2023-10-15 WhiteBoard48, first draft
2023-10-15 Added test code for SPI Flash with FAT filesystem
2023-10-27 Added ESD protection for USB.
2023-10-29 Added test code for USB keyboard
2023-10-29 Rearranged folder structure
2023-10-29 Added test code for USB mouse
2023-10-29 Added test code for rotary encoder
2023-11-12 Added test code for real time clock
2023-11-14 Added README.md
2023-11-26 Added WhiteBoard48 schematic and test code
